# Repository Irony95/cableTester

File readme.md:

### Bill Of Materials
1. 1x all printed parts (9v-BatteryBracket.stl and 9v-BatteryCover.stl excluded)
2. 1x 16-26 (Baseband Connector)
3. 1x 14-1m9 (Data Connector)
4. 7x Eth 5e keystone connector
5. 1x RS232 Male port
6. 10x M3*5 Heat set inserts
7. 10x M3 Nut
8. 20x M3*6 Socket cap screw
9. 1x M3*6 screw ball plunger
10. 1x 3 AA battery Holder
11. Custom PCB
12. Multistrand wire (For port connection)
13. 3x JST-XH 8P Vertical Male connector + female wire
14. 1x JST-XH 2P vertical Male Connector + female wire
15. 8x 0805 330Ω resistor
16. 1x SK12D07 3-pin toggle switch
17. 1x 1*14P 2.54mm Straight female header
18. 1x Raspberry Pi Pico
19. 1x ili9341 Display

#### Note for old version of PCB
resistors R9 to R16 should not be soldered, and VBUS should be shorted to VSYS.
Avoid powering the circuit while plugged into USB.
These issues are fixed for latest PCB.

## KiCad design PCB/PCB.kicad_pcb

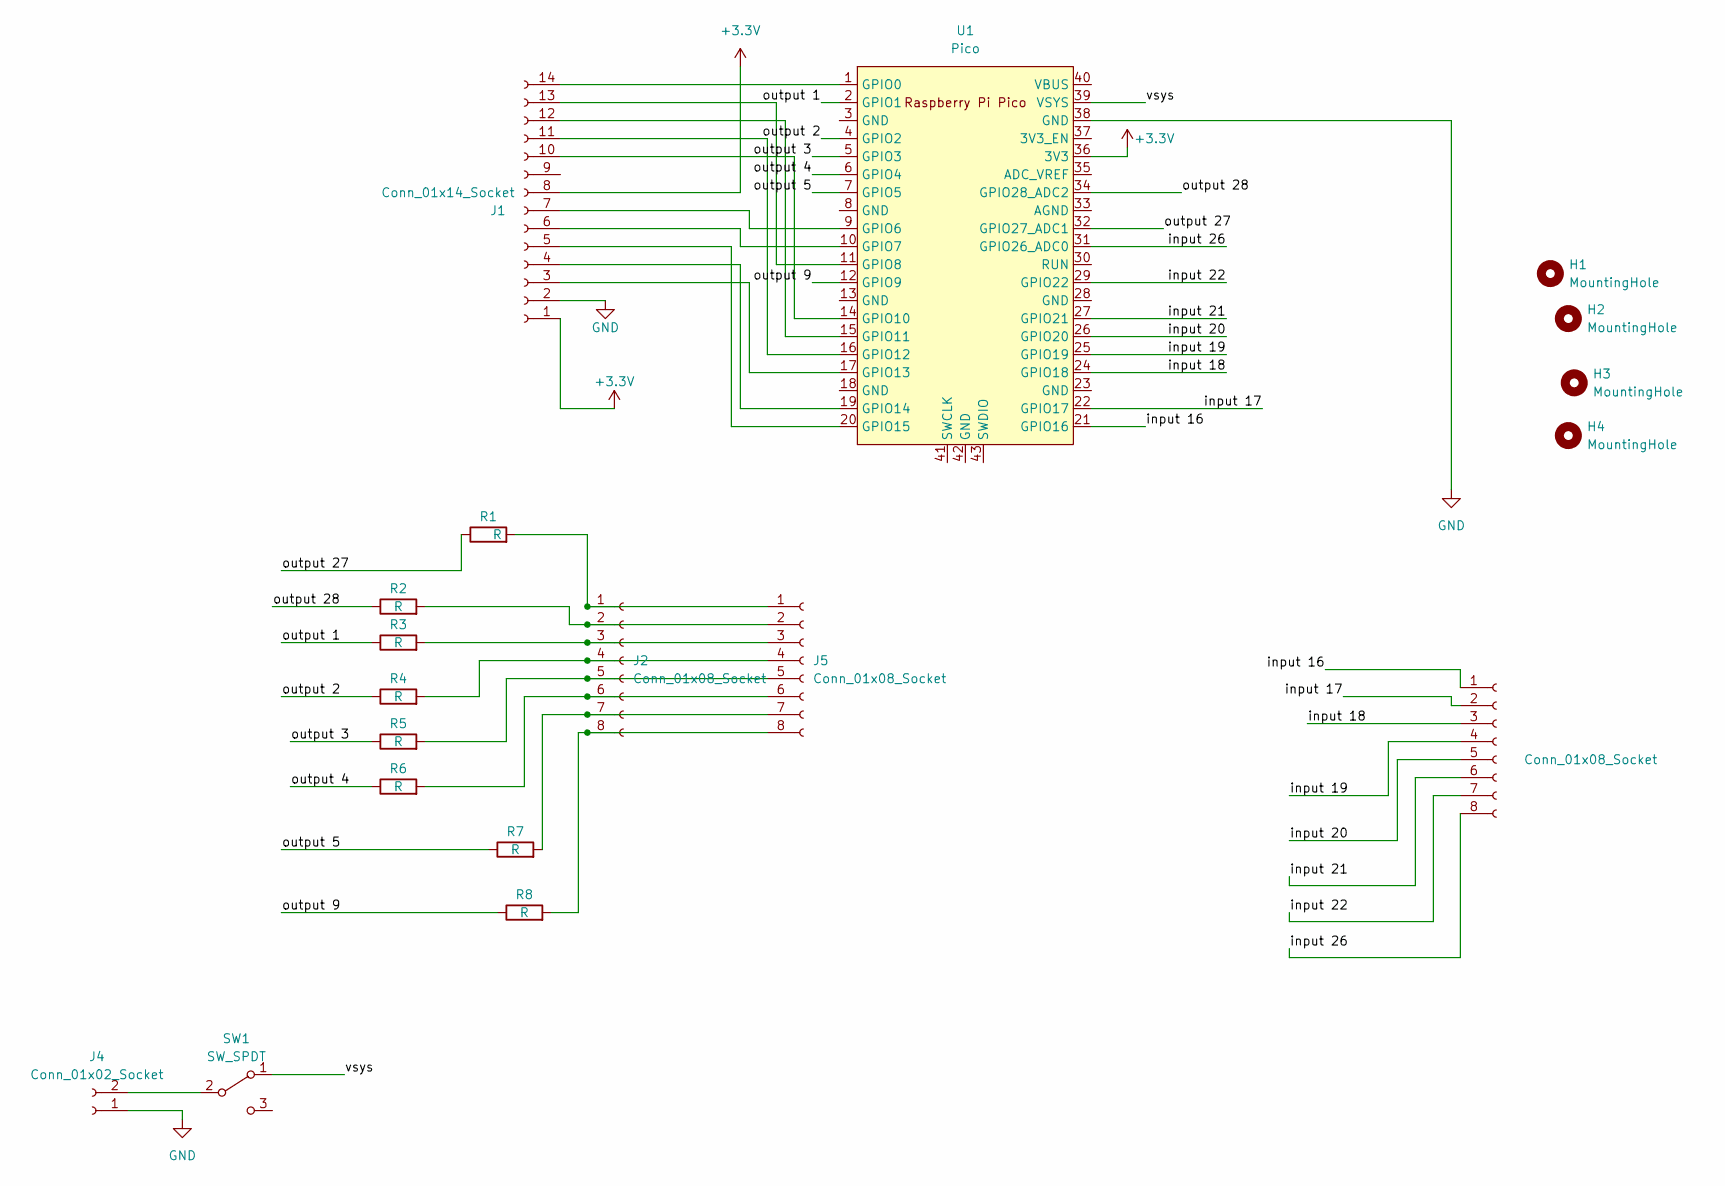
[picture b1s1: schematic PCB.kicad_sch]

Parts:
H1, H2, H3, H4: MountingHole; MountingHole_3.2mm_M3_Pad_TopBottom
J1: Conn_01x14_Socket; PinSocket_1x14_P2.54mm_Vertical
J2, J3, J5: Conn_01x08_Socket; JST_XH_B8B-XH-AM_1x08_P2.50mm_Vertical
J4: Conn_01x02_Socket; JST_XH_B2B-XH-AM_1x02_P2.50mm_Vertical
R1, R2, R3, R4, R5, R6, R7, R8: R; R_0805_2012Metric
SW1: SW_SPDT; SW_Slide_1P2T_CK_OS102011MS2Q
U1: Pico; RPi_Pico_SMD_TH

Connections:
+3.3V: J1.1, J1.8, U1.36 (3V3)
/input 16: J3.1, U1.21 (GPIO16)
/input 17: J3.2, U1.22 (GPIO17)
/input 18: J3.3, U1.24 (GPIO18)
/input 19: J3.4, U1.25 (GPIO19)
/input 20: J3.5, U1.26 (GPIO20)
/input 21: J3.6, U1.27 (GPIO21)
/input 22: J3.7, U1.29 (GPIO22)
/input 26: J3.8, U1.31 (GPIO26_ADC0)
/output 1: R3.1, U1.2 (GPIO1)
/output 2: R4.1, U1.4 (GPIO2)
/output 3: R5.1, U1.5 (GPIO3)
/output 4: R6.1, U1.6 (GPIO4)
/output 5: R7.1, U1.7 (GPIO5)
/output 9: R8.1, U1.12 (GPIO9)
/output 27: R1.1, U1.32 (GPIO27_ADC1)
/output 28: R2.1, U1.34 (GPIO28_ADC2)
/vsys: SW1.1 (A), U1.39 (VSYS)
GND: J1.2, J4.1, U1.38 (GND)
unnamed: J1.3, U1.17 (GPIO13)
unnamed: J1.4, U1.19 (GPIO14)
unnamed: J1.5, U1.20 (GPIO15)
unnamed: J1.6, U1.10 (GPIO7)
unnamed: J1.7, U1.9 (GPIO6)
unnamed: J1.10, U1.14 (GPIO10)
unnamed: J1.11, U1.16 (GPIO12)
unnamed: J1.12, U1.15 (GPIO11)
unnamed: J1.13, U1.11 (GPIO8)
unnamed: J1.14, U1.1 (GPIO0)
unnamed: J2.1, J5.1, R1.2
unnamed: J2.2, J5.2, R2.2
unnamed: J2.3, J5.3, R3.2
unnamed: J2.4, J5.4, R4.2
unnamed: J2.5, J5.5, R5.2
unnamed: J2.6, J5.6, R6.2
unnamed: J2.7, J5.7, R7.2
unnamed: J2.8, J5.8, R8.2
unnamed: J4.2, SW1.2 (B)

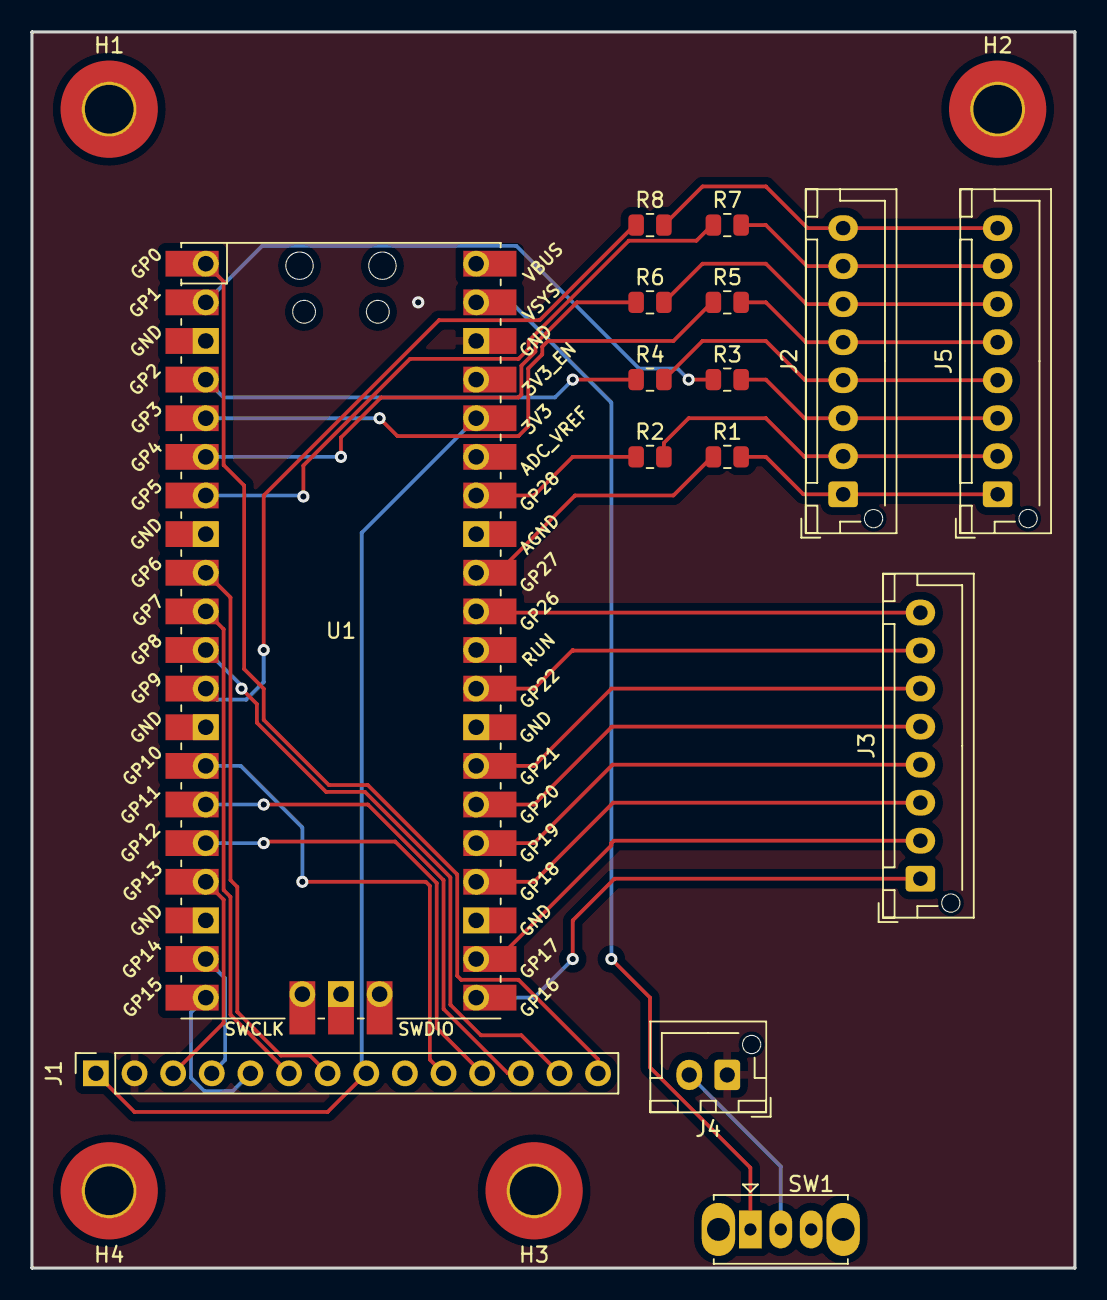
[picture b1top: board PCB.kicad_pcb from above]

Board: 2 copper layers, 68.6 x 81.3 mm, 19 parts (0 on the bottom side), 38 nets.

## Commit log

2025-04-11 first committ
2025-04-14 Created buttons!
2025-04-15 Test draw image and text in buttons
2025-04-16 added main page and cable testing
2025-04-17 Updated UI
2025-04-29 code cleanup
2025-05-07 Mega refactoring of the century. Every page is written as it's own file like a module/object/functonal component
2025-05-09 1) rewrote event loop in main.py 2) moved display.clear() to main event loop 3) add lock "mutex" to prevent race condition
2025-05-09 1) add 2nd home page 2) touch up aesthetics
2025-06-02 squircle
2025-06-04 squircle fix
2025-06-04 button aesthetics
2025-06-04 tiny cleanup
2025-06-07 introduced (probably) finalized 3d model and PCB, along with reorganizing folders
2025-06-07 created bill of materials
2025-06-07 Updated BOM
2025-06-11 clean up and added gpio test file
2025-06-11 minor increase in detail to console
2025-06-12 updated to use internal pull down resistors, remove them from PCB design
2025-06-14 3D model changes, added ETH passthrough and remodelled AA battery bracket
2025-06-18 minor update to readme
2025-07-01 1) print touch x, y to console 2) tweaked touch X and Y min max 3) added an intermediary page, diagram_page. it's current purpose is as a dummy page for when "Test" button is not yet pressed. this is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
2025-07-01 fix typo
2025-07-07 add small delay after turning on or off a pin
